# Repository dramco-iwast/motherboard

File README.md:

# motherboard
Design files (soft- and hardware) for the IWAST motherboard.

Needs reorganization.

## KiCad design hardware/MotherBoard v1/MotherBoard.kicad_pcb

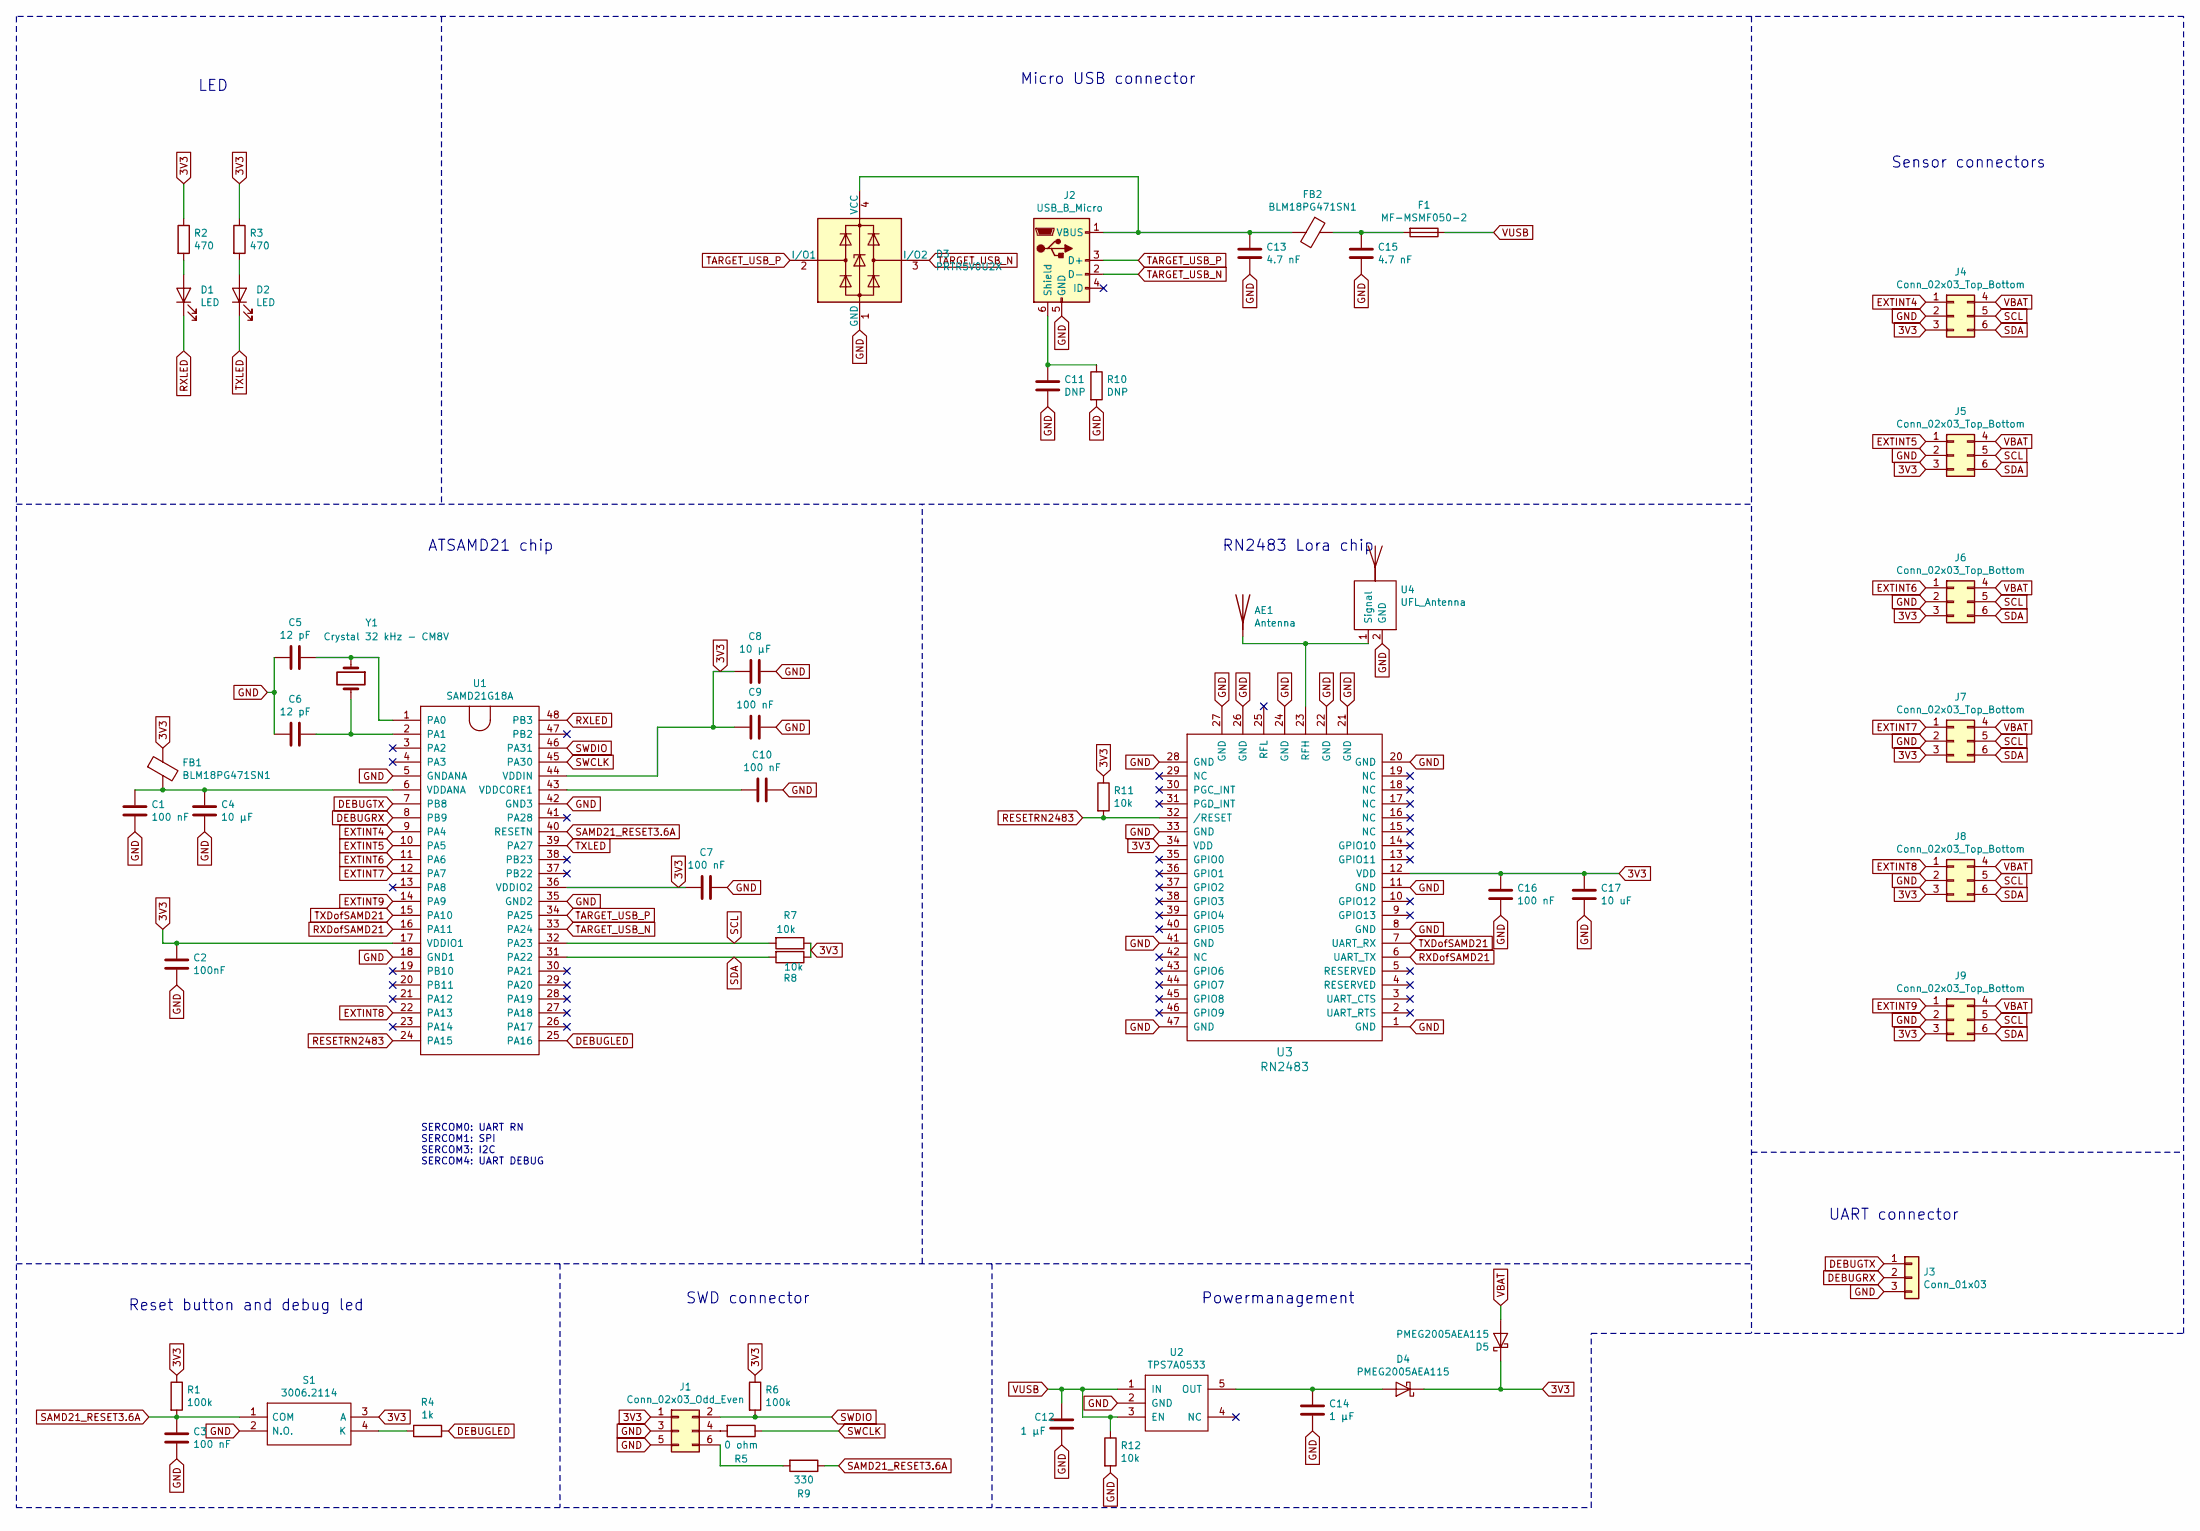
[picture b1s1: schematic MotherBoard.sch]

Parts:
AE1: Antenna; helixAntenna
C1, C3, C7, C9, C10, C16: 100 nF; C_0805_2012Metric_Pad1.15x1.40mm_HandSolder
C2: 100nF; C_0805_2012Metric_Pad1.15x1.40mm_HandSolder
C4, C8: 10 µF; C_0805_2012Metric_Pad1.15x1.40mm_HandSolder
C5, C6: 12 pF; C_0805_2012Metric_Pad1.15x1.40mm_HandSolder
C11: DNP; C_0805_2012Metric_Pad1.15x1.40mm_HandSolder
C12, C14: 1 µF; C_0805_2012Metric_Pad1.15x1.40mm_HandSolder
C13, C15: 4.7 nF; C_0805_2012Metric_Pad1.15x1.40mm_HandSolder
C17: 10 uF; C_0805_2012Metric_Pad1.15x1.40mm_HandSolder
D1, D2: LED; LED_0805_2012Metric_Pad1.15x1.40mm_HandSolder
D3: PRTR5V0U2X; SOT-143
D4, D5: PMEG2005AEA115; PMEG2005
F1: MF-MSMF050-2; MSMF050
FB1, FB2: BLM18PG471SN1; R_0603_1608Metric_Pad1.05x0.95mm_HandSolder
J1: Conn_02x03_Odd_Even; PinHeader_2x03_P2.54mm_Vertical
J2: USB_B_Micro; USB_Micro
J3: Conn_01x03; PinHeader_1x03_P2.54mm_Vertical
J4, J5, J6, J7, J8, J9: Conn_02x03_Top_Bottom; ConnectorHorizontalPcb
R1, R6: 100k; R_0805_2012Metric_Pad1.15x1.40mm_HandSolder
R2, R3: 470; R_0805_2012Metric_Pad1.15x1.40mm_HandSolder
R4: 1k; R_0805_2012Metric_Pad1.15x1.40mm_HandSolder
R5: 0 ohm; R_0805_2012Metric_Pad1.15x1.40mm_HandSolder
R7, R8, R11, R12: 10k; R_0805_2012Metric_Pad1.15x1.40mm_HandSolder
R9: 330; R_0805_2012Metric_Pad1.15x1.40mm_HandSolder
R10: DNP; R_0805_2012Metric_Pad1.15x1.40mm_HandSolder
S1: 3006.2114; 30062114; Manufacturer_Part_Number 3006.2114; Mouser Part Number 979-3006.2114
U1: SAMD21G18A; samd21
U2: TPS7A0533; TPS7A05
U3: RN2483
U4: UFL_Antenna; U.FL_Molex_MCRF_73412-0110_Vertical
Y1: Crystal 32 kHz - CM8V; crystelCM8V

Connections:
3V3: C2.1, C7.2, C8.2, C9.2, C16.1, C17.1, D4.1 (K), D5.1 (K), FB1.1, J1.1, J4.3, J5.3, J6.3, J7.3, J8.3, J9.3, R1.1, R2.1, R3.1, R6.1, R7.1, R8.1, R11.1, S1.3 (A), U1.17 (VDDIO1), U1.36 (VDDIO2), U1.44 (VDDIN), U3.12 (VDD), U3.34 (VDD)
DEBUGLED: R4.2, U1.25 (PA16)
DEBUGRX: J3.2, U1.8 (PB9)
DEBUGTX: J3.1, U1.7 (PB8)
EXTINT4: J4.1, U1.9 (PA4)
EXTINT5: J5.1, U1.10 (PA5)
EXTINT6: J6.1, U1.11 (PA6)
EXTINT7: J7.1, U1.12 (PA7)
EXTINT8: J8.1, U1.22 (PA13)
EXTINT9: J9.1, U1.14 (PA9)
GND: C1.2, C2.2, C3.2, C4.2, C5.2, C6.2, C7.1, C8.1, C9.1, C10.1, C11.2, C12.2, C13.2, C14.2, C15.2, C16.2, C17.2, D3.1 (GND), J1.3, J1.5, J2.5 (GND), J3.3, J4.2, J5.2, J6.2, J7.2, J8.2, J9.2, R10.2, R12.2, S1.2 (N.O.), U1.5 (GNDANA), U1.18 (GND1), U1.35 (GND2), U1.42 (GND3), U2.2 (GND), U3.1 (GND), U3.8 (GND), U3.11 (GND), U3.20 (GND), U3.21 (GND), U3.22 (GND), U3.24 (GND), U3.26 (GND), U3.27 (GND), U3.28 (GND), U3.33 (GND), U3.41 (GND), U3.47 (GND), U4.2 (GND)
unnamed: AE1.1, U3.23 (RFH), U4.1 (Signal)
unnamed: C1.1, C4.1, FB1.2, U1.6 (VDDANA)
unnamed: C5.1, U1.1 (PA0), Y1.1
unnamed: C6.1, U1.2 (PA1), Y1.2
unnamed: C10.2, U1.43 (VDDCORE1)
unnamed: C11.1, J2.6 (Shield), R10.1
unnamed: C13.1, D3.4 (VCC), FB2.2, J2.1 (VBUS)
unnamed: C14.1, D4.2 (A), U2.5 (OUT)
unnamed: C15.1, F1.2, FB2.1
unnamed: D1.2 (A), R2.2
unnamed: D2.2 (A), R3.2
unnamed: J1.4, R5.2
unnamed: J1.6, R9.2
unnamed: R4.1, S1.4 (K)
RESETRN2483: R11.2, U1.24 (PA15), U3.32 (/RESET)
RXDofSAMD21: U1.16 (PA11), U3.6 (UART_TX)
RXLED: D1.1 (K), U1.48 (PB3)
SAMD21_RESET3.6A: C3.1, R1.2, R9.1, S1.1 (COM), U1.40 (RESETN)
SCL: J4.5, J5.5, J6.5, J7.5, J8.5, J9.5, R7.2, U1.32 (PA23)
SDA: J4.6, J5.6, J6.6, J7.6, J8.6, J9.6, R8.2, U1.31 (PA22)
SWCLK: R5.1, U1.45 (PA30)
SWDIO: J1.2, R6.2, U1.46 (PA31)
TARGET_USB_N: D3.3 (I/O2), J2.2 (D-), U1.33 (PA24)
TARGET_USB_P: D3.2 (I/O1), J2.3 (D+), U1.34 (PA25)
TXDofSAMD21: U1.15 (PA10), U3.7 (UART_RX)
TXLED: D2.1 (K), U1.39 (PA27)
VBAT: D5.2 (A), J4.4, J5.4, J6.4, J7.4, J8.4, J9.4
VUSB: C12.1, F1.1, R12.1, U2.1 (IN), U2.3 (EN)

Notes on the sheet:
SERCOM0: UART RN SERCOM1: SPI SERCOM3: I2C SERCOM4: UART DEBUG
Reset button and debug led
SWD connector
Powermanagement
UART connector
Sensor connectors
ATSAMD21 chip
LED
Micro USB connector
RN2483 Lora chip

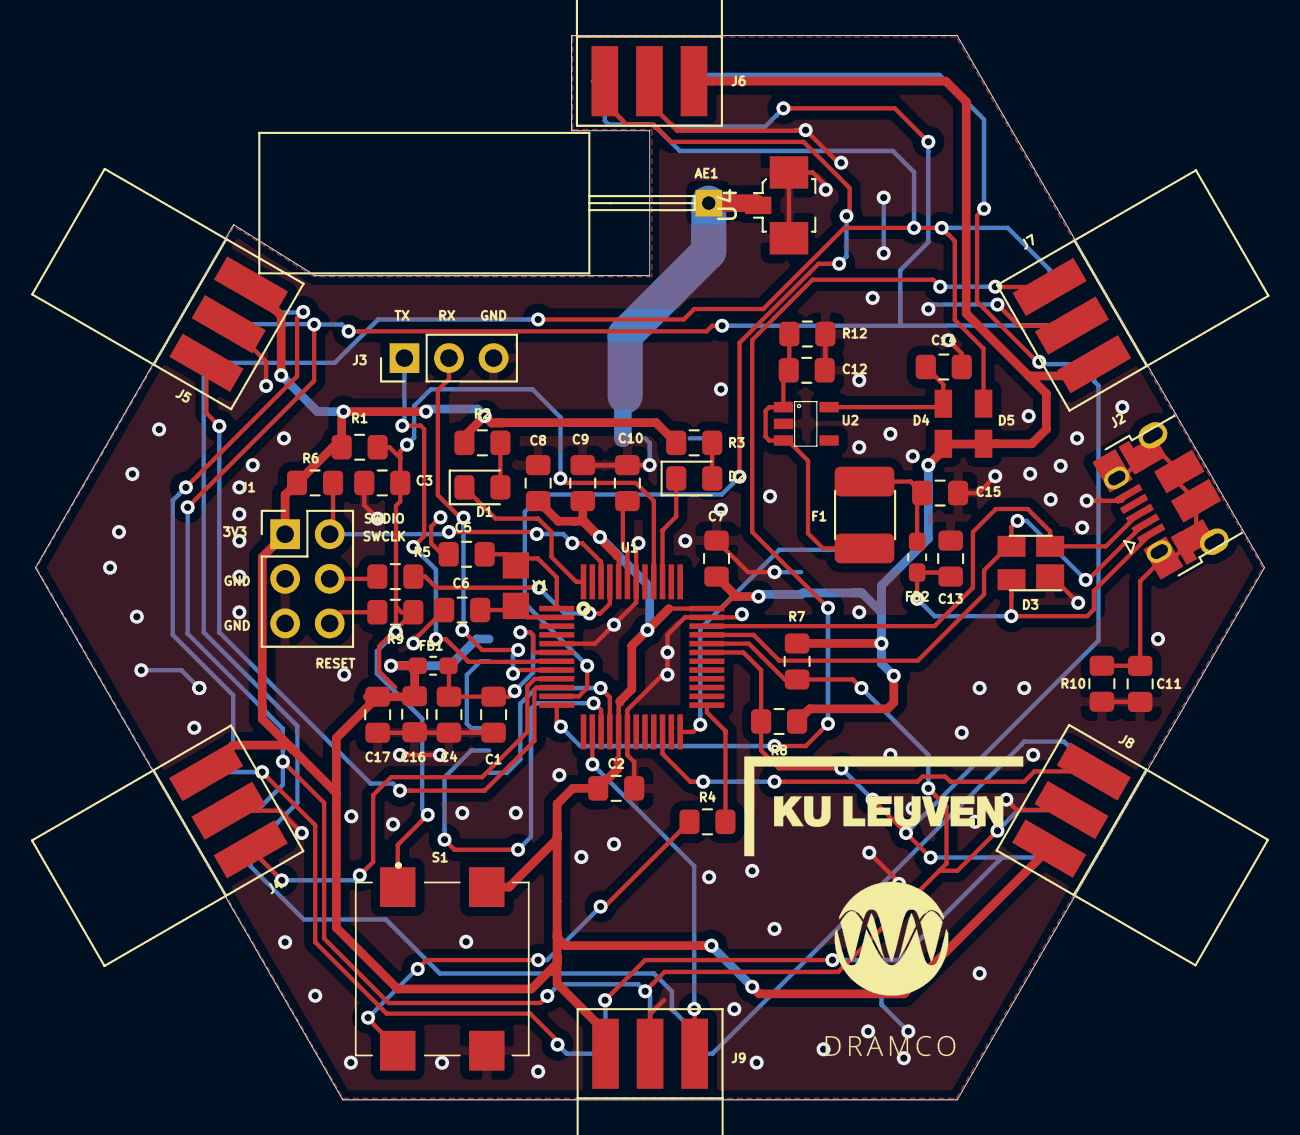
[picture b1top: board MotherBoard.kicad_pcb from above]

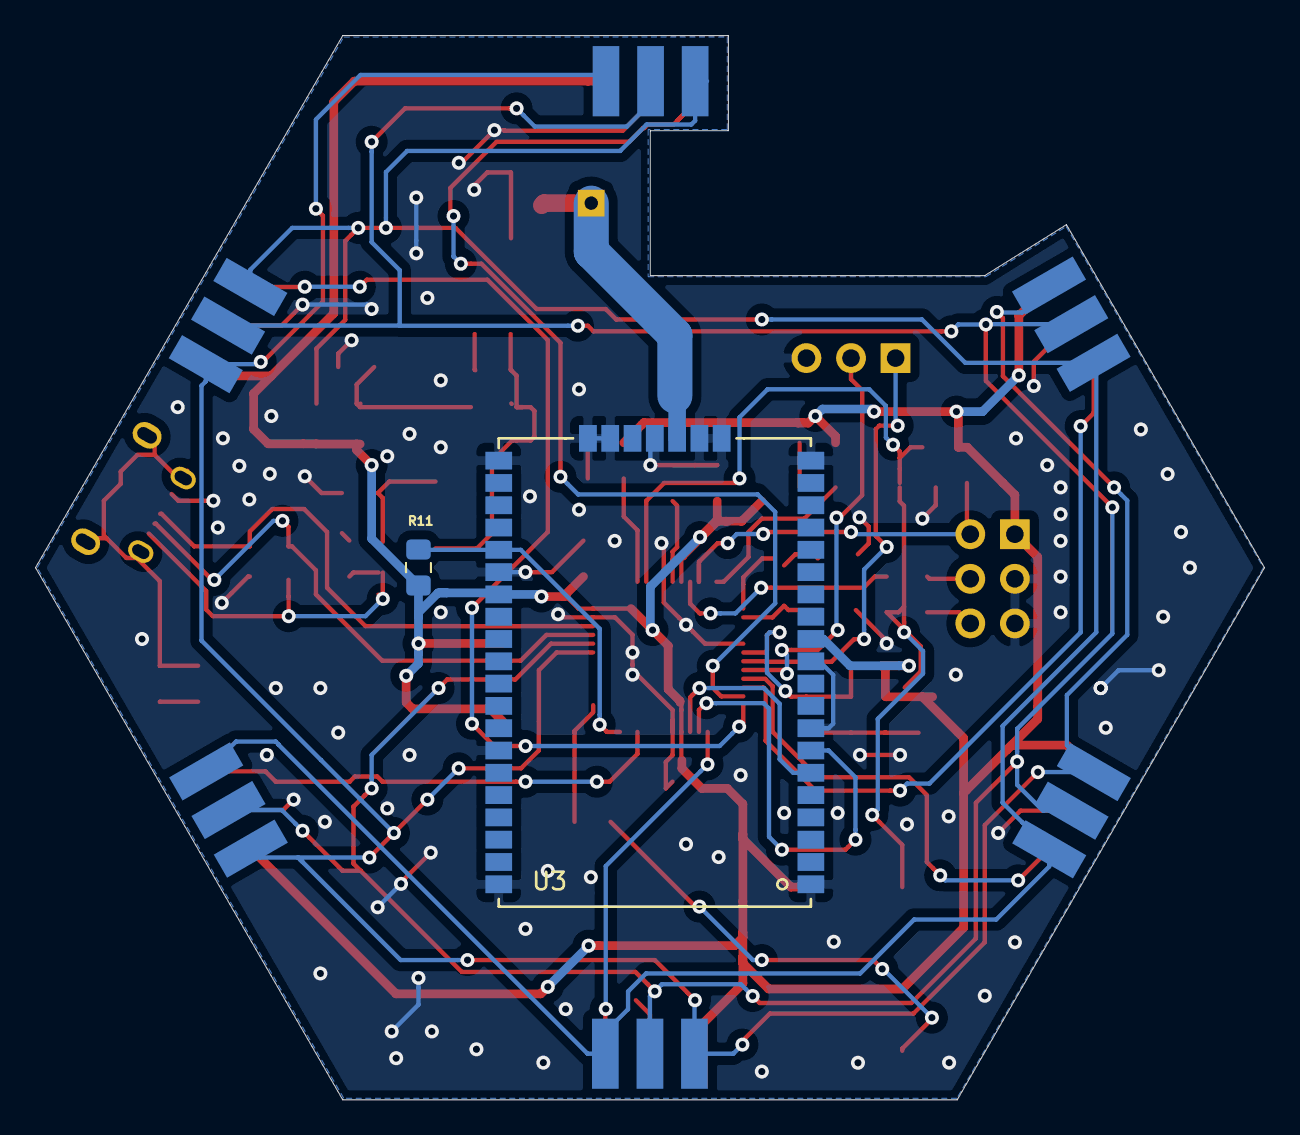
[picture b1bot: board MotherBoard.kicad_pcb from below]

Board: 2 copper layers, 70.0 x 60.6 mm, 53 parts (2 on the bottom side), 39 nets.

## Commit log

2019-10-18 First upload
    Working test of AT command set and non-volatile storage of settings.
2019-10-24 Functionality update
    Added library for LoRaWAN connectivity
    Added Sensor class (not tested yet)
    Added NonVolatileConfig class (not tested yet)
2019-10-24 Removed obsolete files
2019-10-30 Small changes
2019-11-05 Support for polled sensing
    Partly tested (support for multiple metrics/sensor is still under development)
2019-11-07 Small changes
    Some small changes, mainly for testing
2019-11-14 Working NodeManager
    Added extra hardware serial for debugging (because Native USB looses connection in sleep).
    Nodemanager tested with 2 sensors (both polled and interrupt-based operation). Currently no multi-metric sensor support.
2019-11-14 Update main.cpp
    lora test application (working)
2019-11-18 restructured
2019-11-18 Low power testing
2019-11-19 intermediate push
2019-11-20 Temporary update
    Used new low power library.
    Changed file structure of LoRa library.
2019-11-27 Minor updates
    Minor update to NodeManager AT interface
    Temp update of LoraWAN en RN2483
2019-12-10 Modified hardware design of motherboard
2019-12-10 Low-power LoRa operation (modem sleep)
2020-01-15 Testing version
    This version can be used for system testing
2020-01-15 Testing with lora communication
2020-01-20 Bug fix in NodeManager
    Wrong callback for sixth interrupt pin
2020-01-21 LoRaWAN update
2020-01-21 Modified NodeManager loop behaviour.
    Also removed old files
2020-01-23 Modified NonVolatileConfig
2020-08-14 Increased IIC address scan range
2020-10-07 Updated NonVolatileConfig to include data accumulation setting
2020-10-08 Updated NodeManager and LoRaWAN
    Periodic wake-up every 60 seconds. Sleep can be interrupted without impacting the wake-up period.
    Added LED to LoRaWAN library
2020-10-08 Code version updates
2020-10-15 Update platformio.ini
    VERY_LOW_POWER build flag is essential for µA sleep currents
2020-10-15 ArduinoLowPower
    Added time-keeping to ArduinoLowPower
2020-10-15 NodeManager updated
    Improved sleep behavior. Started with support for data accumulation.
2020-10-21 Update ArduinoLowPower
    Sleep() can be used to sleep until previously set alarm
2020-10-21 Update DebugSerial.h
    Added include guards
    Added function to print byte buffer in hex format
2020-10-21 Update NodeManager
    Included status message support
    Updated sleep scheduling
2020-10-22 Update Sensor.cpp
    Clean-up.
2020-10-22 Update Sensor.h
    New define.
2020-10-22 Update platformio.ini
    Add ./src to the include path
2020-10-22 Update NodeManager.h
    New message format parameters.
2020-11-04 Updated NodeManager
    Status messages are sent immediately (even if data accumulation is enabled).
2020-11-04 Update NonVolatileConfig.cpp
    Fixed error with offset in non-volatile config
2020-11-04 Added option to disable status messages
2020-11-04 Added watchdog for stability
    Still in testing phase
2020-11-12 Watchdog reset is used to skip configuration phase
2020-11-12 Updated gitignore
2020-12-14 Motherboard v2
    Made by Guus
2021-01-26 Important updates
    Lora: SF11 = default DR, ADR enabled by default
    Nodemanager: extra wakeup safety added by use of watchdog
2021-01-27 ADR enabled
2021-02-04 NodeManager Update
    Non volatile configuration is only updated when motherboard is reconfigured (by AT commands)
2021-02-19 NodeManager updated
    System reset when connected sensors do not match with the stored configuration.
2021-05-18 Cleanup hardware
2021-06-03 Update LoRaWAN.cpp
    Updated LED control for the new motherboard hardware
2021-06-11 Added option to disable the use of confirmed messages
    Added option to disable the use of confirmed messages as this is not supported by all service providers. Also has an impact on ADR.
2021-09-03 Hardware v2
2021-09-17 Update lora led operation
2022-01-18 Custom ArduinoLowPower
2022-01-18 Updated NonVolatileConfig
    Support for storing Lora-related configuration
2022-01-18 Updated rn2xx3
    Small changes to support (customized) OTAA
2022-01-18 Updated NodeManager
    Supports new AT configuration commands to store and read lora-related settings
2022-01-26 Added hardware v4
2022-02-23 start led board v1
2022-02-23 boardled
2022-02-23 flash couple of times
2022-02-25 added iwast app eui
2022-02-25 moved default adr setting
2022-02-25 Update NodeManager.cpp
    derive board id from deviceEUI
